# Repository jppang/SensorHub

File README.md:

# SensorHub
A sensor hub for X-Track and ON-Track.

Motion Sensors:
MPU-6050, MPU-6500.

Compass Sensors:
QMC5883L, IST8310.

Pressure/Humitidty/Temperature Sensors:
AHT20, BMP280, BME280, MS8607.

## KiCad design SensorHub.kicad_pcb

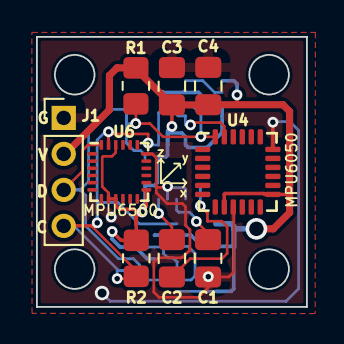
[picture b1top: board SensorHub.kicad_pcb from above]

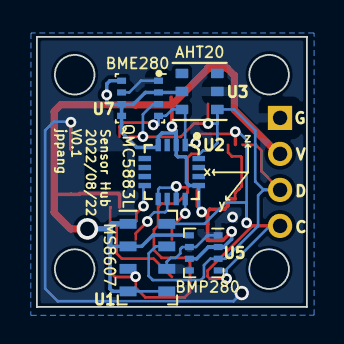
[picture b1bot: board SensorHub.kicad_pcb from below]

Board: 2 copper layers, 15.0 x 15.0 mm, 14 parts (5 on the bottom side), 7 nets.

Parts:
C1, C3: 4.7uF; C_0805_2012Metric_Pad1.18x1.45mm_HandSolder
C2: 0.22uF; C_0805_2012Metric_Pad1.18x1.45mm_HandSolder
C4: 0.1uF; C_0805_2012Metric_Pad1.18x1.45mm_HandSolder
J1: Conn_01x04; PinHeader_1x04_P2.00mm_Vertical
R1, R2: 4.7K; R_0805_2012Metric_Pad1.20x1.40mm_HandSolder
U1: MS5611-01BA; LGA-8_3x5mm_P1.25mm
U2: HMC5883L; PLCC16-0.5-3X3MM
U3: AHT20; PSON100P300X300X110-6N
U4: MPU-6050; InvenSense_QFN-24_4x4mm_P0.5mm
U5: BMP280; Bosch_LGA-8_2x2.5mm_P0.65mm_ClockwisePinNumbering
U6: MPU-9250; InvenSense_QFN-24_3x3mm_P0.4mm
U7: BME280; Bosch_LGA-8_2.5x2.5mm_P0.65mm_ClockwisePinNumbering

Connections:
/3V3: C3.1, C4.1, J1.2, R1.1, R2.1, U1.1 (VDD), U1.2 (PS), U1.4 (CSB), U1.5 (CSB), U2.2 (2(VDD)), U2.4 (4(S1)), U2.13 (13(VDDIO)), U3.2 (VDD), U4.8 (VDDIO), U4.13 (VDD), U5.2 (CSB), U5.6 (VDDIO), U5.8 (VDD), U6.8 (VDDIO), U6.9 (AD0/MISO), U6.13 (VDD), U6.22 (~CS), U7.2 (CSB), U7.5 (SDO), U7.6 (VDDIO), U7.8 (VDD)
/SCL: J1.4, R2.2, U1.8 (SCLK), U2.1 (1(SCL)), U3.3 (SCL), U4.23 (SCL), U5.4 (SCK), U6.23 (SCL/SCLK), U7.4 (SCK)
/SDA: J1.3, R1.2, U1.7 (SDI/SDA), U2.16 (16(SDA)), U3.4 (SDA), U4.24 (SDA), U5.3 (SDI), U6.24 (SDA/MOSI), U7.3 (SDI)
GND: C1.2, C3.2, C4.2, J1.1, U1.3 (GND), U1.6 (SDO), U2.9 (9(GND)), U2.11 (11(GND)), U3.5 (GND), U4.9 (AD0), U4.18 (GND), U5.1 (GND), U5.5 (SDO), U5.7 (GND), U6.18 (GND), U7.1 (GND), U7.7 (GND)
unnamed: C1.1, U2.10 (10(C1))
unnamed: C2.1, U2.12 (12(SETC))
unnamed: C2.2, U2.8 (8(SETP))

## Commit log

2022-09-18 Add files via upload
    Sensor Hub created by KiCad 6.
2022-09-18 Update README.md
    Supported sensors.
